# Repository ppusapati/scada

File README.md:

# SCADA System - Water & Solar Management

A full-stack SCADA (Supervisory Control and Data Acquisition) system for monitoring and controlling Water Treatment and Solar Energy infrastructure.

## Architecture

```
┌─────────────────────────────────────────────────────────────────┐
│                    SCADA System Architecture                     │
├─────────────────────────────────────────────────────────────────┤
│                                                                  │
│  ┌──────────────┐    ┌──────────────┐    ┌──────────────────┐   │
│  │   Svelte      │◄──►│   Go Backend │◄──►│   PostgreSQL     │   │
│  │   Frontend    │WS  │   (REST+WS)  │    │   + TimescaleDB  │   │
│  │   Dashboard   │    │              │    │                  │   │
│  └──────────────┘    └──────┬───────┘    └──────────────────┘   │
│                             │                                    │
│                        MQTT Broker                               │
│                        (Mosquitto)                               │
│                             │                                    │
│              ┌──────────────┼──────────────┐                    │
│              │              │              │                     │
│  ┌───────────▼──┐ ┌────────▼───┐ ┌───────▼────────┐           │
│  │ Water Sensors │ │Solar Panels│ │ Flow Meters    │           │
│  │ (Rust FW)    │ │(Rust FW)   │ │ (Rust FW)      │           │
│  └──────────────┘ └────────────┘ └────────────────┘           │
│                                                                  │
└─────────────────────────────────────────────────────────────────┘
```

## Tech Stack

| Layer      | Technology        | Purpose                          |
|------------|-------------------|----------------------------------|
| Frontend   | SvelteKit 2       | Real-time SCADA HMI Dashboard    |
| Backend    | Go 1.22+          | REST API, WebSocket, MQTT Bridge |
| Database   | PostgreSQL + TimescaleDB | Time-series + relational data |
| IoT Comm   | MQTT (Mosquitto)  | Device communication protocol    |
| Embedded   | Rust              | Sensor/actuator firmware         |
| Deploy     | Docker + Docker Compose | Container orchestration     |

## Phases

- **Phase 1**: Backend API, Database, MQTT integration
- **Phase 2**: Svelte frontend dashboard with real-time data
- **Phase 3**: Rust embedded firmware for sensors
- **Phase 4**: Alarms, historical data, reporting
- **Phase 5**: Advanced HMI, PLC integration, deployment

## Quick Start

```bash
# Start infrastructure
docker-compose up -d

# Run backend
cd backend && go run cmd/server/main.go

# Run frontend
cd frontend && npm run dev
```

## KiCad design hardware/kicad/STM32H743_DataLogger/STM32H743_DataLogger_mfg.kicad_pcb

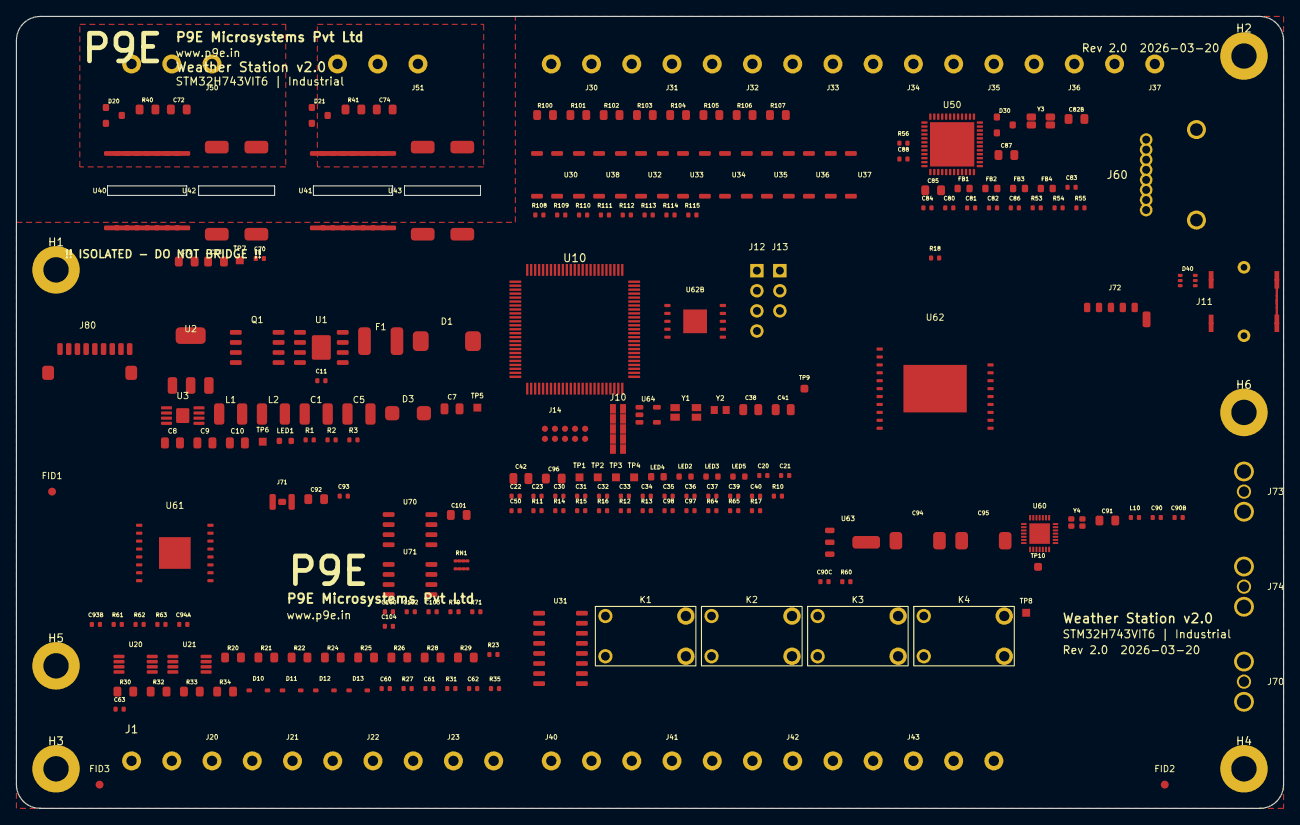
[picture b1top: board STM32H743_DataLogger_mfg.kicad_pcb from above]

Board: 4 copper layers, 160.0 x 100.0 mm, 231 parts (0 on the bottom side), 164 nets, no tracks yet.

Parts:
C1: 10uF/50V; C_1210_3225Metric
C5: 22uF/10V; C_1210_3225Metric
C7, C9, C10, C71, C72, C73, C74, C82B, C85, C91, C92, C96, C101: 10uF; C_0805_2012Metric
C8: 22uF; C_0805_2012Metric
C11, C30, C31, C32, C33, C34, C35, C36, C37, C50, C60, C61, C62, C63, C70, C80, C81, C82, C86, C88, C90, C93, C93B, C94A, C97, C98, C100, C102, C103, C104: 100nF; C_0402_1005Metric
C20, C21: 15pF; C_0402_1005Metric
C22, C23, C90C: 6.8pF; C_0402_1005Metric
C38, C87: 4.7uF; C_0805_2012Metric
C39: 1uF_VDDA; C_0402_1005Metric
C40: 100nF_VDDA; C_0402_1005Metric
C41: 2.2uF_VCAP1; C_0805_2012Metric
C42: 2.2uF_VCAP2; C_0805_2012Metric
C83, C84: 18pF; C_0402_1005Metric
C90B: 5.6pF; C_0402_1005Metric
C94, C95: 100uF; CP_Elec_6.3x5.8
D1: SMDJ36A; D_SMC
D3: SS34; D_SMA
D10, D11, D12, D13: PESD5V0S1BA; D_SOD-323
D20, D21: PESD2CAN; D_SOT-23_ANK
D30: PESD5V0S2BT; D_SOT-23_ANK
D40: PRTR5V0U2X; D_SOT-363_SC-70-6
F1: 1.5A_PTC; Fuse_1812_4532Metric
FB1, FB2, FB3, FB4: BLM18PG121; L_0603_1608Metric
FID1, FID2, FID3: Fiducial; Fiducial_1mm_Dia_2.54mm_Outer
H1, H2, H3, H4: M3_Mount; MountingHole_3.2mm_M3_Pad_Via
H5, H6: DIN_Mount; MountingHole_3.2mm_M3_Pad_Via
J1: 24VDC_Input; TerminalBlock_Phoenix_MKDS-1,5-2-5.08_1x02_P5.08mm_Horizont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
J10: SWD_Debug; PinHeader_2x05_P1.27mm_Vertical_SMD
J11: USB-C; USB_C_Receptacle_GCT_USB4085
J12: UART_Debug; PinHeader_1x04_P2.54mm_Vertical
J13: BOOT0_Select; PinHeader_1x03_P2.54mm_Vertical
J14: TC2050-IDC; Tag-Connect_TC2050-IDC-FP_2x05_P1.27mm_Vertical
J20: AI_CH0; TerminalBlock_Phoenix_MKDS-1,5-2-5.08_1x02_P5.08mm_Horizont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
J21: AI_CH1; TerminalBlock_Phoenix_MKDS-1,5-2-5.08_1x02_P5.08mm_Horizont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
J22: AI_CH2; TerminalBlock_Phoenix_MKDS-1,5-2-5.08_1x02_P5.08mm_Horizont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
J23: AI_CH3; TerminalBlock_Phoenix_MKDS-1,5-2-5.08_1x02_P5.08mm_Horizont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
J30: DI_0; TerminalBlock_Phoenix_MKDS-1,5-2-5.08_1x02_P5.08mm_Horizont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
J31: DI_1; TerminalBlock_Phoenix_MKDS-1,5-2-5.08_1x02_P5.08mm_Horizont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
J32: DI_2; TerminalBlock_Phoenix_MKDS-1,5-2-5.08_1x02_P5.08mm_Horizont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
J33: DI_3; TerminalBlock_Phoenix_MKDS-1,5-2-5.08_1x02_P5.08mm_Horizont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
J34: DI_4; TerminalBlock_Phoenix_MKDS-1,5-2-5.08_1x02_P5.08mm_Horizont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
J35: DI_5; TerminalBlock_Phoenix_MKDS-1,5-2-5.08_1x02_P5.08mm_Horizont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
J36: DI_6; TerminalBlock_Phoenix_MKDS-1,5-2-5.08_1x02_P5.08mm_Horizont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
J37: DI_7; TerminalBlock_Phoenix_MKDS-1,5-2-5.08_1x02_P5.08mm_Horizont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
J40: DO_0; TerminalBlock_Phoenix_MKDS-1,5-3-5.08_1x03_P5.08mm_Horizont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
J41: DO_1; TerminalBlock_Phoenix_MKDS-1,5-3-5.08_1x03_P5.08mm_Horizont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
J42: DO_2; TerminalBlock_Phoenix_MKDS-1,5-3-5.08_1x03_P5.08mm_Horizont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
J43: DO_3; TerminalBlock_Phoenix_MKDS-1,5-3-5.08_1x03_P5.08mm_Horizont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
J50: RS485; TerminalBlock_Phoenix_MKDS-1,5-3-5.08_1x03_P5.08mm_Horizont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
J51: CAN; TerminalBlock_Phoenix_MKDS-1,5-3-5.08_1x03_P5.08mm_Horizont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
J60: J0011D21BNL; RJ45_Pulse_JXD0-0019NL
J70: SMA_LoRa; SMA_Amphenol_132289_EdgeMount
J71: U.FL_WiFi; U.FL_Hirose_U.FL-R-SMT-1_Solder
J72: NanoSIM; SIM_Nano_Molex_503398-1892
J73: SMA_LTE; SMA_Amphenol_132289_EdgeMount
J74: SMA_GNSS; SMA_Amphenol_132289_EdgeMount
J80: microSD; microSD_HC_Molex_104031-0811
K1, K2, K3, K4: HF46F-G/5-HS1T; Relay_SPST_HF46F-G_Form_A
L1: 10uH; L_1210_3225Metric
L2: 22uH; L_1210_3225Metric
L10: 5.6nH; L_0402_1005Metric
LED1: Green_PWR; LED_0603_1608Metric
LED2: Blue_STATUS; LED_0603_1608Metric
LED3: Red_ERROR; LED_0603_1608Metric
LED4: Orange COMM; LED_0603_1608Metric
LED5: Blue_BLE; LED_0603_1608Metric
Q1: SI4435DDY; SO-8_3.9x4.9mm_P1.27mm
R1: 52.3k; R_0402_1005Metric
R2, R10, R11, R16, R18, R53, R54, R55, R60, R61, R62, R63, R64, R108, R109, R110, R111, R112, R113, R114, R115: 10k; R_0402_1005Metric
R3, R12, R13, R17, R23, R27, R31, R35, R65: 1k; R_0402_1005Metric
R14, R15: 33R; R_0402_1005Metric
R20, R24, R28, R32: 249R; R_0805_2012Metric
R21, R25, R29, R33: 20k; R_0805_2012Metric
R22, R26, R30, R34: 10k; R_0805_2012Metric
R40, R41: 120R; R_0805_2012Metric
R56: 12.4k 1%; R_0402_1005Metric
R70, R71: 4.7k; R_0402_1005Metric
R100, R101, R102, R103, R104, R105, R106, R107: 4.7k; R_0805_2012Metric
RN1: 47k_x4; R_Array_Convex_4x0402
TP1: +3V3; TestPoint_Pad_1.0x1.0mm
TP2: +5V; TestPoint_Pad_1.0x1.0mm
TP3: +3V3A; TestPoint_Pad_1.0x1.0mm
TP4: GND; TestPoint_Pad_1.0x1.0mm
TP5: SWDIO; TestPoint_Pad_1.0x1.0mm
TP6: SWCLK; TestPoint_Pad_1.0x1.0mm
TP7: NRST; TestPoint_Pad_1.0x1.0mm
TP8: BOOT0; TestPoint_Pad_1.0x1.0mm
TP9: GSM_RI; TestPoint_Pad_1.0x1.0mm
TP10: LORA_DIO1; TestPoint_Pad_1.0x1.0mm
U1: TPS54560; HSOP-8-1EP_3.9x4.9mm_P1.27mm_EP2.41x3.1mm
U2: TLV1117LV33; SOT-223-3_TabPin2
U3: TPS7A4533; MSOP-8-1EP_3x3mm_P0.65mm_EP1.68x1.88mm
U10: STM32H743VIT6; LQFP-100_14x14mm_P0.5mm
U20, U21: OPA2376; MSOP-8_3x3mm_P0.65mm
U30, U32, U33, U34, U35, U36, U37, U38: TLP293; SOP-4_3.8x4.1mm_P2.54mm
U31: ULN2003A; SOIC-16_3.9x9.9mm_P1.27mm
U40: ISO3082; SOIC-16W_7.5x10.3mm_P1.27mm
U41: ISO1042; SOIC-16W_7.5x10.3mm_P1.27mm
U42, U43: NXJ1S0505MC; Converter_DCDC_NXJ1S_SMD
U50: W5500; QFN-48-1EP_7x7mm_P0.5mm_EP5.6x5.6mm
U60: SX1276; QFN-28-1EP_4x4mm_P0.4mm
U61: ATWINC1500; Microchip_ATWINC15x0-MR210xB
U62: SIM7600G-H; SIMCom_SIM7600
U62B: RN4870; Microchip_RN4870
U63: TPS73641; SOT-223-3_TabPin2
U64: TPS3823-33; SOT-23-5
U70: W25Q64JV; SOIC-8_3.9x4.9mm_P1.27mm
U71: AT24C256C; SOIC-8_3.9x4.9mm_P1.27mm
Y1, Y3: 25MHz; Crystal_SMD_3215-4Pin_3.2x1.5mm
Y2: 32.768kHz; Crystal_SMD_2012-2Pin_2.0x1.2mm
Y4: 32MHz; Crystal_SMD_2016-4Pin_2.0x1.6mm

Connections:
+3V3: C8.1, C30.1, C31.1, C32.1, C33.1, C34.1, C35.1, C36.1, C37.1, C38.1, C70.1, C80.1, C81.1, C82.1, C82B.1, C90.1, C91.1, C92.1, C93.1, C93B.1, C96.1, C97.1, C98.1, C100.1, C101.1, C102.1, C103.1, C104.1, J10.1, J12.1, J13.3, J14.1, J80.6, LED1.1, LED4.2, R10.1, R53.1, R54.1, R55.1, R60.1, R61.1, R62.1, R63.1, R64.1, R70.1, R71.1, R108.1, R109.1, R110.1, R111.1, R112.1, R113.1, R114.1, R115.1, RN1.1, RN1.2, RN1.3, RN1.4, TP1.1, U2.2, U2.4, U10.6, U10.11, U10.27, U10.50, U10.75, U10.100, U40.1, U41.1, U50.4, U50.8, U50.11, U50.15, U50.17, U50.21, U50.28, U60.10, U60.12, U60.16, U60.20, U60.22, U60.24, U60.26, U60.28, U61.1, U61.13, U61.15, U62B.4, U64.1, U70.3, U70.7, U70.8, U71.8
+3V3A: C10.1, C39.1, C40.1, TP3.1, U3.5, U3.6, U10.20, U10.21, U20.8, U21.8
+4V1: C94.1, C95.1, U62.1, U62.2, U63.2, U63.4
+5V: C5.1, C7.1, C9.1, C71.1, C73.1, J11.A4, J11.A9, J11.B4, J11.B9, L2.2, R1.1, TP2.1, U2.3, U3.1, U42.2, U43.2, U63.1
+24V: C1.1, D1.1, F1.1, F1.2, J1.1, K1.2, K2.2, K3.2, K4.2, L1.1, L1.2, Q1.1, Q1.2, Q1.3, Q1.5, Q1.6, Q1.7, Q1.8, U1.2, U31.9
ADC1_CH0: U10.22, U20.1, U20.2
ADC1_CH1: U10.23, U20.6, U20.7
ADC1_CH2: U10.24, U21.1, U21.2
ADC1_CH3: U10.25, U21.6, U21.7
AI_CH0_FILT: R21.2, R22.1, R23.1
AI_CH0_IN: C60.1, R23.2, U20.3
AI_CH0_RAW: D10.1, J20.1, R20.1, R21.1
AI_CH1_FILT: R25.2, R26.1, R27.1
AI_CH1_IN: C61.1, R27.2, U20.5
AI_CH1_RAW: D11.1, J21.1, R24.1, R25.1
AI_CH2_FILT: R29.2, R30.1, R31.1
AI_CH2_IN: C62.1, R31.2, U21.3
AI_CH2_RAW: D12.1, J22.1, R28.1, R29.1
AI_CH3_FILT: R33.2, R34.1, R35.1
AI_CH3_IN: C63.1, R35.2, U21.5
AI_CH3_RAW: D13.1, J23.1, R32.1, R33.1
BLE_RST: R64.2, U10.59, U62B.5
BLE_STATUS: LED5.1, U10.60, U62B.6
BOOT0: J13.2, R11.1, R16.1, TP8.1, U10.94
CAN_H: D21.1, J51.1, R41.1, U41.11
CAN_ISO_GND: C74.2, D21.3, J51.3, U41.9, U41.10, U41.13, U41.14, U43.3
CAN_ISO_VCC: C74.1, U41.15, U41.16, U43.4
CAN_L: D21.2, J51.2, R41.2, U41.12
DI_0: R108.2, U10.84, U30.4
DI_0_ISO: J30.1, R100.1
DI_0_LED: R100.2, U30.1
DI_1: R109.2, U10.88, U38.4
DI_1_ISO: J31.1, R101.1
DI_1_LED: R101.2, U38.1
DI_2: R110.2, U10.97, U32.4
DI_2_ISO: J32.1, R102.1
DI_2_LED: R102.2, U32.1
DI_3: R111.2, U10.98, U33.4
DI_3_ISO: J33.1, R103.1
DI_3_LED: R103.2, U33.1
DI_4: R112.2, U10.39, U34.4
DI_4_ISO: J34.1, R104.1
DI_4_LED: R104.2, U34.1
DI_5: R113.2, U10.40, U35.4
DI_5_ISO: J35.1, R105.1
DI_5_LED: R105.2, U35.1
DI_6: R114.2, U10.41, U36.4
DI_6_ISO: J36.1, R106.1
DI_6_LED: R106.2, U36.1
DI_7: R115.2, U10.42, U37.4
DI_7_ISO: J37.1, R107.1
DI_7_LED: R107.2, U37.1
DI_COM: J30.2, J31.2, J32.2, J33.2, J34.2, J35.2, J36.2, J37.2, U30.2, U32.2, U33.2, U34.2, U35.2, U36.2, U37.2, U38.2
DO0_COM: J40.2, K1.3
DO0_NO: J40.1, K1.4
DO1_COM: J41.2, K2.3
DO1_NO: J41.1, K2.4
DO2_COM: J42.2, K3.3
DO2_NO: J42.1, K3.4
DO3_COM: J43.2, K4.3
DO3_NO: J43.1, K4.4
DO_0: U10.43, U31.1
DO_1: U10.44, U31.2
DO_2: U10.45, U31.3
DO_3: U10.61, U31.4
ETH_INT: R55.2, U10.34, U50.36
ETH_RST: R54.2, U10.2, U50.37
ETH_RXN: FB4.1, U50.5
ETH_RXN_F: FB4.2, J60.6
ETH_RXP: FB3.1, U50.6
ETH_RXP_F: D30.2, FB3.2, J60.3
ETH_TXN: FB2.1, U50.1
ETH_TXN_F: FB2.2, J60.2
ETH_TXP: FB1.1, U50.2
ETH_TXP_F: D30.1, FB1.2, J60.1
FDCAN1_RX: U10.81, U41.4
FDCAN1_TX: U10.82, U41.2
GND: C1.2, C5.2, C7.2, C8.2, C9.2, C10.2, C20.2, C21.2, C22.2, C23.2, C30.2, C31.2, C32.2, C33.2, C34.2, C35.2, C36.2, C37.2, C38.2, C39.2, C40.2, C41.2, C42.2, C50.2, C60.2, C61.2, C62.2, C63.2, C70.2, C71.2, C73.2, C80.2, C81.2, C82.2, C82B.2, C83.2, C84.2, C85.2, C86.2, C87.2, C88.2, C90.2, C90B.2, C90C.2, C91.2, C92.2, C93.2, C93B.2, C94.2, C94A.2, C95.2, C96.2, C97.2, C98.2, C100.2, C101.2, C102.2, C103.2, C104.2, D1.2, D3.1, D10.2, D11.2, D12.2, D13.2, D30.3, D40.3, D40.4, H1.1, H2.1, H3.1, H4.1, H5.1, H6.1, J1.2, J10.3, J10.5, J10.9, J11.A1, J11.A12, J11.B1, J11.B12, J11.S1, J11.S2, J12.4, J13.1, J14.3, J14.5, J14.9, J20.2, J21.2, J22.2, J23.2, J60.4, J60.5, J60.7, J60.8, J60.SH1, J60.SH2, J70.2, J70.3, J71.2, J71.3, J72.C5, J72.SH, J73.2, J73.3, J74.2, J74.3, J80.8, J80.SH1, J80.SH2, Q1.4, R2.2, R3.2, R11.2, R12.2, R13.2, R16.2, R17.2, R18.2, R20.2, R22.2, R24.2, R26.2, R28.2, R30.2, R32.2, R34.2, R56.2, R65.2, TP4.1, U1.7, U1.9, U2.1, U3.2, U3.9, U10.10, U10.19, U10.26, U10.49, U10.74, U10.99, U20.4, U21.4, U30.3, U31.8, U32.3, U33.3, U34.3, U35.3, U36.3, U37.3, U38.3, U40.2, U40.7, U40.8, U41.3, U41.5, U41.6, U41.7, U41.8, U42.1, U43.1, U50.3, U50.9, U50.14, U50.16, U50.19, U50.29, U50.43, U50.44, U50.45, U50.48, U50.49, U60.1, U60.9, U60.11, U60.15, U60.18, U60.19, U60.21, U60.23, U60.25, U60.27, U60.29, U61.2, U61.10, U61.12, U61.14, U61.16, U61.17, U62.3, U62.10, U62.15, U62.17, U62.19, U62.20, U62.EP, U62B.1, U62B.7, U62B.8, U62B.9, U62B.10, U62B.11, U63.3, U64.2, U70.4, U71.1, U71.2, U71.3, U71.4, Y1.2, Y1.4, Y3.2, Y3.4, Y4.2, Y4.4
GNSS_ANT: J74.1, U62.18
GSM_DTR: R18.1, U62.6
GSM_PWR_KEY: U10.47, U62.8
GSM_RI: TP9.1, U62.7
GSM_STATUS: U10.58, U62.9
HSE_IN: C20.1, U10.12, Y1.1
HSE_OUT: C21.1, U10.13, Y1.3
I2C1_SCL: R71.2, U10.92, U71.6
I2C1_SDA: R70.2, U10.93, U71.5
LED_COMM: LED4.1, R17.1
LORA_ANT: C90B.1, J70.1, L10.1, U60.17
LORA_DIO0: U10.7, U60.7
LORA_DIO1: TP10.1, U60.8
LORA_RST: U10.46, U60.6
LORA_XTAL1: U60.13, Y4.1
LORA_XTAL2: U60.14, Y4.3
LSE_IN: C22.1, U10.8, Y2.1
LSE_OUT: C23.1, U10.9, Y2.2
LTE_ANT_MAIN: J73.1, U62.16
NRST: C50.1, J10.10, J14.10, R10.2, TP7.1, U10.14, U64.4
NSS_ETH: R53.2, U10.3, U50.32
NSS_FLASH: U10.77, U70.1
NSS_LORA: R60.2, U10.28, U60.5
NSS_WIFI: R63.2, U10.51, U61.9
RS485_A: D20.1, J50.1, R40.1, U40.12
RS485_B: D20.2, J50.2, R40.2, U40.13
RS485_DE: U10.85, U40.4, U40.5
RS485_ISO_GND: C72.2, D20.3, J50.3, U40.9, U40.10, U40.15, U42.3
RS485_ISO_VCC: C72.1, U40.16, U42.4
SDMMC1_CLK: J80.5, U10.80
SDMMC1_CMD: J80.7, RN1.7, U10.83
SDMMC1_D0: J80.1, RN1.5, U10.65
SDMMC1_D1: J80.2, RN1.6, U10.66
SDMMC1_D2: J80.3, RN1.8, U10.78
SDMMC1_D3: J80.4, U10.79
SD_CD: J80.CD, U10.62
SIM_CLK: D40.5, J72.C3, U62.13
SIM_DATA: D40.2, J72.C7, U62.14
SIM_RST: D40.6, J72.C2, U62.12
SIM_VCC: D40.1, J72.C1, U62.11
SPI1_MISO: U10.30, U60.3
SPI1_MOSI: U10.91, U60.4
SPI1_SCK: U10.29, U60.2
SPI2_MISO: U10.53, U61.7
SPI2_MOSI: U10.54, U61.8
SPI2_SCK: U10.52, U61.6
SPI3_MISO: U10.90, U70.2
SPI3_MOSI: U10.36, U70.5
SPI3_SCK: U10.89, U70.6
SPI4_MISO: U10.4, U50.34
SPI4_MOSI: U10.5, U50.35
SPI4_SCK: U10.1, U50.33
SWCLK: J10.4, J14.4, TP6.1, U10.76
SWDIO: J10.2, J14.2, TP5.1, U10.72
UART4_RX: U10.95, U62.5
UART4_TX: U10.96, U62.4
UART7_RX: U10.37, U62B.3
UART7_TX: U10.38, U62B.2
ULN_DO0: K1.1, U31.16
ULN_DO1: K2.1, U31.15
ULN_DO2: K3.1, U31.14
ULN_DO3: K4.1, U31.13
USART1_RX: R15.1, U10.69
USART1_RX_BUF: J12.3, R15.2
USART1_TX: R14.1, U10.68
USART1_TX_BUF: J12.2, R14.2
USART2_RX: U10.87, U40.3
USART2_TX: U10.86, U40.6
USB_DM: J11.A7, U10.70
USB_DP: J11.A6, U10.71
VBUCK_BST: C11.1, U1.1
VBUCK_SW: C11.2, D3.2, L2.1, U1.8
VCAP1: C41.1, U10.48
VCAP2: C42.1, U10.73
VFB: R1.2, R2.1, U1.5
W5500_1V8OUT: C85.1, C86.1, U50.22
W5500_EXRES: R56.1, U50.10
W5500_TOCAP: C87.1, U50.20
W5500_VBG: C88.1, U50.18
W5500_XTAL1: C83.1, U50.30, Y3.1
W5500_XTAL2: C84.1, U50.31, Y3.3
WDT_KICK: U10.56, U64.3
WIFI_ANT: J71.1, U61.11
WIFI_EN: R61.2, U10.35, U61.3
WIFI_IRQ: U10.57, U61.5
WIFI_RST: C94A.1, R62.2, U10.15, U61.4

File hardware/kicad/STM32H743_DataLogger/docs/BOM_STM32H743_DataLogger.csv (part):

Reference,Qty,Value,Description,Package/Footprint,MPN,Manufacturer,Category,Unit Price (USD),Ext Price (USD),Datasheet
"=== MCU & CORE ===",,,,,,,,,,,
U10,1,STM32H743VIT6,"ARM Cortex-M7 480MHz, 2MB Flash, 1MB SRAM MCU",LQFP-100,STM32H743VIT6,STMicroelectronics,MCU,12.50,12.50,https://www.st.com/resource/en/datasheet/stm32h743vi.pdf
Y1,1,25MHz,"HSE Crystal Oscillator, 10ppm, 10pF load",SMD 3215-4Pin,ABM8-25.000MHZ-B2-T,Abracon,Crystal,0.45,0.45,
Y2,1,32.768kHz,"LSE Crystal for RTC, 12.5pF load",SMD 2012,ABS07-32.768KHZ-T,Abracon,Crystal,0.35,0.35,
J10,1,SWD Debug,"10-pin ARM Cortex SWD debug connector",2x05 1.27mm SMD,FTSH-105-01-L-DV-K,Samtec,Connector,2.80,2.80,
J11,1,USB-C,"USB Type-C 2.0 receptacle for programming",USB-C SMD,USB4085-GF-A,GCT,Connector,0.65,0.65,
U64,1,TPS3823-33DBVR,"External hardware watchdog timer, 1.6s timeout, 3.3V supervisor",SOT-23-5,TPS3823-33DBVR,Texas Instruments,Supervisor IC,0.85,0.85,https://www.ti.com/lit/ds/symlink/tps3823.pdf
J12,1,UART Debug,"4-pin 2.54mm debug console header (TX/RX/VCC/GND)",2.54mm 1x04,PH1-04-UA,Adam Tech,Connector,0.15,0.15,
J13,1,BOOT0 Jumper,"3-pin 2.54mm jumper header for BOOT0 select",2.54mm 1x03,PH1-03-UA,Adam Tech,Connector,0.10,0.10,
J14,1,TC2050-IDC,"Tag-Connect 10-pin no-legs programming footprint",TC2050-IDC,TC2050-IDC-NL,Tag-Connect,Connector,0.00,0.00,
"R14-R15",2,33R,"UART series resistors (ESD protection)",0402,RC0402FR-0733RL,Yageo,Resistor,0.01,0.02,
R16,1,10k,"BOOT0 pull-down resistor (redundant safety)",0402,RC0402FR-0710KL,Yageo,Resistor,0.01,0.01,
"=== POWER SUPPLY ===",,,,,,,,,,,
J1,1,24VDC Input,"Phoenix Contact screw terminal 2-pin",5.08mm pitch,1729128,Phoenix Contact,Connector,0.85,0.85,
F1,1,1.5A PTC,"Resettable PTC fuse, 1.5A hold",1812,MF-MSMF150-2,Bourns,Protection,0.30,0.30,
D1,1,SMDJ36A,"TVS diode, 36V standoff, 600W peak",SMC,SMDJ36A,Littelfuse,Protection,0.55,0.55,
Q1,1,SI4435DDY,"P-Channel MOSFET for reverse polarity protection",SO-8,SI4435DDY-T1-GE3,Vishay,MOSFET,0.75,0.75,
L1,1,"10uH 2A","EMI filter ferrite inductor",1210,SRN3015TA-100M,Bourns,Inductor,0.25,0.25,
U1,1,TPS54560DDAR,"Buck converter 4.5-60V to 5V, 5A",HSOP-8,TPS54560DDAR,Texas Instruments,Power IC,3.20,3.20,https://www.ti.com/lit/ds/symlink/tps54560.pdf
L2,1,"22uH 3A","Buck converter inductor, shielded",1210,SRP1265A-220M,Bourns,Inductor,0.85,0.85,
D3,1,SS34,"Schottky diode 40V 3A for buck converter",SMA,SS34,ON Semiconductor,Diode,0.15,0.15,
U2,1,TLV1117LV33,"LDO 3.3V 1A, digital power rail",SOT-223,TLV1117LV33DCYR,Texas Instruments,Power IC,0.45,0.45,
U3,1,TPS7A4533,"Ultra-low-noise LDO 3.3V, analog power rail",MSOP-8-EP,TPS7A4533DGNR,Texas Instruments,Power IC,2.15,2.15,
LED1,1,Green PWR,"Power indicator LED, green",0603,19-217/GHC-YR1S2/3T,Everlight,LED,0.05,0.05,
R3,1,1k,"LED current limiting resistor",0402,RC0402FR-071KL,Yageo,Resistor,0.01,0.01,
"=== POWER SUPPLY PASSIVES ===",,,,,,,,,,,
C1,2,"10uF/50V X7R","Buck input capacitors",1210,GRM32ER71H106KA12L,Murata,Capacitor,0.35,0.70,
C5,2,"22uF/10V X5R","Buck output capacitors",1210,GRM32ER61A226ME20L,Murata,Capacitor,0.25,0.50,
R1,1,"52.3k 1%","Feedback divider top (buck converter)",0402,RC0402FR-0752K3L,Yageo,Resistor,0.01,0.01,
R2,1,"10k 1%","Feedback divider bottom (buck converter)",0402,RC0402FR-0710KL,Yageo,Resistor,0.01,0.01,
C7,1,"10uF/10V","3.3V LDO input capacitor",0805,GRM21BR61A106ME51L,Murata,Capacitor,0.10,0.10,
C8,1,"22uF/6.3V","3.3V LDO output capacitor",0805,GRM21BR60J226ME39L,Murata,Capacitor,0.12,0.12,
C9,1,"10uF/10V","Analog LDO input capacitor",0805,GRM21BR61A106ME51L,Murata,Capacitor,0.10,0.10,
C10,1,"10uF/6.3V","Analog LDO output capacitor",0805,GRM21BR60J106ME19L,Murata,Capacitor,0.12,0.12,
"=== MCU DECOUPLING (per AN4938) ===",,,,,,,,,,,
"C30-C37",8,100nF,"VDD decoupling capacitors",0402,GRM155R71C104KA88D,Murata,Capacitor,0.02,0.16,
C38,1,4.7uF,"VDD bulk decoupling",0805,GRM21BR61C475KA73L,Murata,Capacitor,0.08,0.08,
C39,1,1uF,"VDDA decoupling",0402,GRM155R61A105ME01D,Murata,Capacitor,0.03,0.03,
C40,1,100nF,"VDDA decoupling",0402,GRM155R71C104KA88D,Murata,Capacitor,0.02,0.02,
"C41-C42",2,2.2uF,"VCAP1/VCAP2 capacitors",0805,GRM21BR61A225KA73L,Murata,Capacitor,0.06,0.12,
"C20-C21",2,15pF,"HSE load capacitors",0402,GRM1555C1H150GA01D,Murata,Capacitor,0.02,0.04,
"C22-C23",2,6.8pF,"LSE load capacitors",0402,GRM1555C1H6R8BA01D,Murata,Capacitor,0.02,0.04,
C11,1,100nF,"Buck bootstrap capacitor (BST-SW)",0402,GRM155R71C104KA88D,Murata,Capacitor,0.02,0.02,
C50,1,100nF,"NRST filter capacitor",0402,GRM155R71C104KA88D,Murata,Capacitor,0.02,0.02,
R10,1,10k,"NRST pull-up resistor",0402,RC0402FR-0710KL,Yageo,Resistor,0.01,0.01,
R11,1,10k,"BOOT0 pull-down resistor",0402,RC0402FR-0710KL,Yageo,Resistor,0.01,0.01,
C98,1,100nF,"TPS3823 watchdog decoupling",0402,GRM155R71C104KA88D,Murata,Capacitor,0.02,0.02,
"=== STATUS LEDs ===",,,,,,,,,,,
LED2,1,Blue,"Status LED blue",0603,19-213/BHC-ZL1M2RY/3T,Everlight,LED,0.06,0.06,
LED3,1,Red,"Error LED red",0603,19-213/R6C-AL1M2VY/3T,Everlight,LED,0.05,0.05,
LED4,1,Orange,"Communication activity LED",0603,19-213/Y2C-CQ2R2L/3T,Everlight,LED,0.06,0.06,
"R12-R13/R17",3,1k,"LED current limiting (STS/ERR/COMM)",0402,RC0402FR-071KL,Yageo,Resistor,0.01,0.03,
"=== ANALOG INPUTS (4ch) ===",,,,,,,,,,,
"J20-J23",4,AI Input,"Analog input terminal blocks",5.08mm 2-pin,1729128,Phoenix Contact,Connector,0.85,3.40,
"D10-D13",4,PESD5V0S1BA,"ESD protection TVS per AI channel",SOD-323,"PESD5V0S1BA,115",Nexperia,Protection,0.08,0.32,
"R20/R24/R28/R32",4,"249R 0.1%","4-20mA shunt resistors (precision)",0805,ERA-6AEB2490V,Panasonic,Resistor,0.25,1.00,
"R21/R25/R29/R33",4,"20k 0.1%","Voltage divider top (0-10V mode)",0805,ERA-6AEB2002V,Panasonic,Resistor,0.20,0.80,
"R22/R26/R30/R34",4,"10k 0.1%","Voltage divider bottom (0-10V mode)",0805,ERA-6AEB1002V,Panasonic,Resistor,0.20,0.80,
"R23/R27/R31/R35",4,1k,"Anti-aliasing filter resistors",0402,RC0402FR-071KL,Yageo,Resistor,0.01,0.04,
"C60-C63",4,"100nF C0G","Anti-aliasing filter capacitors (low distortion)",0402,GRM1555C1H104JA01D,Murata,Capacitor,0.04,0.16,
"U20-U21",2,OPA2376AIDGKR,"Dual rail-to-rail op-amp, low offset, precision buffer",MSOP-8,OPA2376AIDGKR,Texas Instruments,Op-Amp,2.50,5.00,
"=== DIGITAL INPUTS (8ch) ===",,,,,,,,,,,
"J30-J37",8,DI Input,"Digital input terminal blocks",5.08mm 2-pin,1729128,Phoenix Contact,Connector,0.85,6.80,
"R100-R107",8,4.7k,"Optocoupler LED current limiting (24V/4.5mA)",0805,RC0805JR-074K7L,Yageo,Resistor,0.02,0.16,
"U30,U32-U38",8,"TLP293(GR","Optocoupler isolator (3.75kVrms)",SOP-4,"TLP293(GR-TPL,E",Toshiba,Isolator,0.45,3.60,
R18,1,10k,"SIM7600 DTR pull-down (hold modem awake)",0402,RC0402FR-0710KL,Yageo,Resistor,0.01,0.01,
"R108-R115",8,10k,"Optocoupler output pull-up resistors",0402,RC0402FR-0710KL,Yageo,Resistor,0.01,0.08,
"=== DIGITAL OUTPUTS (4ch) ===",,,,,,,,,,,
U31,1,ULN2003AIDR,"7-ch Darlington transistor array driver",SOIC-16,ULN2003AIDR,Texas Instruments,Driver IC,0.35,0.35,
"K1-K4",4,HF46F-G/5-HS1T,"SPST-NO relay 5A/250VAC",THT SIP,HF46F-G/5-HS1T,Hongfa,Relay,1.50,6.00,
"J40-J43",4,DO Output,"Relay output terminal blocks (NO/COM)",5.08mm 3-pin,1729131,Phoenix Contact,Connector,1.20,4.80,
"=== RS485 INTERFACE (Isolated) ===",,,,,,,,,,,
U40,1,ISO3082DWR,"Isolated RS-485 transceiver (5kVrms)",SOIC-16W,ISO3082DWR,Texas Instruments,Interface IC,3.85,3.85,
R40,1,120R,"RS485 bus termination (jumper selectable)",0805,RC0805FR-07120RL,Yageo,Resistor,0.02,0.02,
D20,1,PESD2CAN,"RS485 bus ESD protection",SOT-23,"PESD2CAN,215",Nexperia,Protection,0.12,0.12,
J50,1,RS485 A/B/GND,"RS485 bus terminal block",5.08mm 3-pin,1729131,Phoenix Contact,Connector,1.20,1.20,
C70,1,100nF,"ISO3082 MCU-side decoupling",0402,GRM155R71C104KA88D,Murata,Capacitor,0.02,0.02,
"=== ISOLATED BUS-SIDE SUPPLIES ===",,,,,,,,,,,
"U42-U43",2,NXJ1S0505MC-R13,"1W isolated 5V-5V DC-DC 5.2kVDC (RS485/CAN bus side)",SMD,NXJ1S0505MC-R13,Murata,Power,4.90,9.80,
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
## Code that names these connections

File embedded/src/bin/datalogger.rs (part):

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
    // SX1276 LoRa control pins
    let _lora_cs = Output::new(p.PA4, Level::High, Speed::VeryHigh);
    let _lora_rst = Output::new(p.PC2, Level::High, Speed::Low);
    let _lora_dio0 = Input::new(p.PC13, Pull::Down);

    // ATWINC1500 WiFi control pins
    let _wifi_cs = Output::new(p.PB12, Level::High, Speed::VeryHigh);
    let _wifi_rst = Output::new(p.PC0, Level::High, Speed::Low); // Moved from PB2 (now SPI3_MOSI)
    let _wifi_en = Output::new(p.PB1, Level::High, Speed::Low);
    let _wifi_irq = Input::new(p.PD10, Pull::Up);

    // W25Q64JV Flash CS (SPI3 remapped: PB3=SCK, PB4=MISO, PB2=MOSI)
    let _flash_cs = Output::new(p.PA15, Level::High, Speed::VeryHigh);

    // W5500 Ethernet control pins
    let _eth_cs = Output::new(p.PE4, Level::High, Speed::VeryHigh);
    let mut eth_rst = Output::new(p.PE3, Level::High, Speed::Low);
    let _eth_int = Input::new(p.PB0, Pull::Up);

    // SIM7600 GSM control pins
    let _gsm_pwr_key = Output::new(p.PC3, Level::Low, Speed::Low);
    let _gsm_status = Input::new(p.PD11, Pull::Down);

    // RN4870 BLE control pins
    let _ble_rst = Output::new(p.PD12, Level::High, Speed::Low);
    let _ble_status = Input::new(p.PD13, Pull::Down);

    // RS485 DE/RE pin
    let _rs485_de = Output::new(p.PD4, Level::Low, Speed::High);

    // Digital outputs (relay drivers via ULN2003)
    let _do0 = Output::new(p.PD14, Level::Low, Speed::Low);
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    // ---- SDMMC1 SD Card Pins ----
    // Native SDMMC1 peripheral in 4-bit mode for high-speed SD card access
    // Pins configured as alternate function by embassy-stm32 SDMMC driver:
    //   PC12 = SDMMC1_CLK
    //   PD2  = SDMMC1_CMD
    //   PC8  = SDMMC1_D0
    //   PC9  = SDMMC1_D1
    //   PC10 = SDMMC1_D2
    //   PC11 = SDMMC1_D3
    // Card detect via Molex 104031-0811 connector CD pin
    info!("SDMMC1 pins reserved for SD card (4-bit mode)");

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
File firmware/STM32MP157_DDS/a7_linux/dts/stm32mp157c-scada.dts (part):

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     *   - Water variant: ADS1258 (24-bit, 8x 4-20mA inputs)
     *
     * Pin mapping:
     *   PA5  = SPI1_SCK   (AF5)
     *   PA6  = SPI1_MISO  (AF5)
     *   PA7  = SPI1_MOSI  (AF5)
     *   PA4  = SPI1_NSS   (GPIO, active low CS)
     *   PB0  = ADC_DRDY   (GPIO input, active low)
     *   PB1  = ADC_RESET  (GPIO output, active low)
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     * used for ambient/enclosure temperature monitoring.
     *
     * Pin mapping:
     *   PB6 = I2C1_SCL (AF4)
     *   PB7 = I2C1_SDA (AF4)
     *
     * TMP117 I2C address: 0x48 (ADD0 = GND)
     * Clock: 400 kHz (Fast mode)
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     * Modbus RTU slave communication with legacy field devices.
     *
     * Pin mapping:
     *   PA2 = USART2_TX  (AF7)
     *   PA3 = USART2_RX  (AF7)
     *   PA1 = RS485_DE   (GPIO output, direction enable)
     *
     * Default baud rate: 9600 (configurable via Modbus holding register)
     * Format: 8N1 (8 data bits, no parity, 1 stop bit)
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
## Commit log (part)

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2026-02-26 feat: Complete SCADA system for Water and Solar management
    Full-stack SCADA system with Go backend, Svelte frontend, Rust embedded firmware, MQTT communication, TimescaleDB, Docker and Kubernetes deployment.
    https://claude.ai/code/session_019Wy25xaq74CdfxNhnp2sEB
2026-02-26 feat: Add Clean Architecture, ConnectRPC, and Circuit Breaker
    - Domain layer: entities, value objects, enums, repository interfaces, domain errors
    - Use cases: water, solar, alarm, auth, reading with business logic validation
    - ConnectRPC: Full protobuf schema (scada.proto) with 6 services, ConnectRPC handlers,
    auth/role/logging/recovery interceptors, h2c HTTP/2 server
    - Circuit Breaker: Generic implementation with closed/open/half-open states,
    configurable thresholds, registry for monitoring, repository wrappers
2026-03-01 docs: Add hardware docs, cost estimation, and DDS upgrade design
    https://claude.ai/code/session_019Wy25xaq74CdfxNhnp2sEB
2026-03-01 feat: Complete implementation across all layers - frontend, backend DDS, embedded HAL, STM32MP157 firmware
    Frontend (Svelte):
    - Full dashboard with KPI cards, gauges, and trend charts
    - Water RTU page with tank gauge, pump/valve controls, sensor cards
    - Solar SMU page with power gauge, string table, energy charts
    - Alarms page with filtering, acknowledgment, and audio notifications
    - History page with device/metric selectors, date range, CSV export
2026-03-06 fix: Harden security, fix critical bugs, and improve code quality
    - Remove hardcoded credentials; require DB_PASSWORD and JWT_SECRET env vars
    - Move WebSocket endpoint behind auth middleware with query param token support
    - Restrict WebSocket CheckOrigin to allowed origins
    - Disable anonymous MQTT access, require password file
    - Replace hardcoded Docker Compose secrets with env var references
    - Add secrets.yaml to .gitignore, provide .example templates
2026-03-15 feat: Add STM32H743 PLC-grade data logger PCB design in KiCad
    Complete hardware design for an industrial PLC-grade data logger featuring:
    MCU: STM32H743VIT6 (ARM Cortex-M7, 480MHz, 2MB Flash, 1MB SRAM)
    Communications:
    - Ethernet 10/100 (LAN8742A PHY + RJ45 w/ magnetics)
    - LoRa 868/915MHz (RFM95W/SX1276 via SPI)
    - BLE 5.0 + WiFi 802.11bgn (ESP32-C3-MINI-1)
2026-03-15 feat: Upgrade to full industrial-grade components and SPI architecture
    Major design changes for PLC-grade reliability:
    Component Upgrades:
    - Replace ESP32-C3 dual-MCU with ATWINC1500 WiFi (SPI2) + RN4870 BLE (UART7)
    Eliminates second processor, both rated -40 to +85°C industrial
    - Replace LAN8742A RMII PHY with W5500 SPI Ethernet controller
    Hardwired TCP/IP stack, frees 11 RMII pins, simpler firmware
2026-03-15 feat: Add complete STM32H743 Embassy firmware for PLC-grade data logger
    Full no_std embedded firmware with feature-gated dual-target build:
    - HAL drivers: SX1276 LoRa, ATWINC1500 WiFi, RN4870 BLE, W5500 Ethernet,
    SIM7600G-H GSM, RS485 Modbus RTU (CRC-16), CAN FD
    - Peripherals: 4ch ADC with 4-20mA/0-10V, 8x optocoupled DI, 4x relay DO,
    TPS3823-33 hardware watchdog, SPI bus configs, UART ports
    - Storage: W25Q64JV flash ring buffer, microSD FAT32 logging, AT24C256 EEPROM
2026-03-15 feat: Add SD card data storage with SDMMC1 native 4-bit mode
    - Rewrote microsd.rs with full SDMMC1 native driver: 4-bit mode on
    PC8-PC12/PD2, card type detection (SDv1/v2/SDHC), write buffering
    (4KB), file rotation by size (10MB default), statistics tracking
    - Added sd_logger.rs: high-level CSV data logging with automatic file
    rotation (LOG_0000.CSV through LOG_0999.CSV), buffered writes for
    SD card longevity, error recovery, config/calibration backup support
2026-03-15 feat: Add programming interface headers (J12-J14) to PCB
    Schematic additions (STM32H743_MCU.kicad_sch):
    - J12: UART debug console header (4-pin 2.54mm: VCC/TX/RX/GND)
    USART1 on PA9(TX)/PA10(RX) at 115200 baud, FTDI cable compatible
    33R series resistors (R14/R15) for ESD protection
    - J13: BOOT0 select jumper (3-pin: GND-BOOT0-3V3)
    GND position = normal flash boot (default via R16 10k pull-down)
2026-03-15 feat: Add flash protection lockdown and OTA firmware update system
    Security module (embedded/src/security/):
    - flash_protection.rs: STM32H743 option byte management for post-
    provisioning lockdown. After first firmware install:
    - RDP Level 1: SWD cannot read flash (reversing mass-erases chip)
    - BOOT0 locked via option byte: DFU bootloader inaccessible
    - Write protection on bootloader sector (Bank 1, Sector 0)
2026-03-19 feat: Add manufacturing-ready PCB layout with gerber generation
    Add mfg-optimized KiCad PCB layout with proper DFM constraints,
    assembly documentation, and automated gerber generation script.
    - STM32H743_DataLogger_mfg.kicad_pcb: 4-layer stackup, ENIG finish,
    controlled impedance, fiducials, and manufacturing annotations
    - Assembly_Notes_mfg.md: Fab specs, BOM notes, and assembly instructions
    - generate_gerbers.sh: Automated gerber/drill/BOM/pick-place export
2026-03-19 fix: Complete U10 MCU pads, fix connectors and series resistor nets
    - Add all 100 LQFP pads for STM32H743VIT6 with correct net assignments
    - Add pad definitions for J10 SWD, J11 USB-C, J14 Tag-Connect
    - Fix R14/R15 series resistors (were same-net on both pads)
    - Add USART1_TX_BUF/USART1_RX_BUF intermediate nets
    WIP: Peripheral sections, routing, vias, and zones still needed.
    https://claude.ai/code/session_01XsiZ6LJT6X46LKY8yEbRbx
2026-03-20 feat: Complete all PCB sections - Ethernet, Wireless, Storage, I/O, Fieldbus
    Add all remaining component footprints to manufacturing PCB:
    - Ethernet: W5500, RJ45 (J60), 25MHz crystal, ferrite beads, ESD
    - Wireless: SX1276 LoRa, ATWINC1500 WiFi, RN4870 BLE, SIM7600G LTE
    - Storage: microSD slot, W25Q64 NOR Flash, AT24C256 EEPROM
    - Analog Inputs: 4-ch with ESD, precision resistors, OPA2376 buffer
    - Digital I/O: 8 optocoupled inputs, ULN2003 + relay outputs
2026-03-20 feat: Add P9E silkscreen branding, fix BOM/schematic cross-check issues
    - Add complete silkscreen: P9E branding (3.5mm bold), company name,
    website, product info (Weather Station v2.0), functional area labels,
    connector pin labels, LED labels, compliance marks on back
    - Fix BOM: add missing J12/J13/J14/R14-R16, resolve LED4 duplicate
    (renamed to LED5 for BLE), fix C101 conflict with C104
    - Complete analog input schematic channels 1-3 (TVS, precision resistors,
